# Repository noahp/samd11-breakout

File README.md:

[![GitHub Workflow
Status](https://img.shields.io/github/workflow/status/noahp/samd11-breakout/main-ci?style=for-the-badge)](https://github.com/noahp/samd11-breakout/actions)

# samd11 breakout

Little breakout for some spare samd11's.

Trying out https://debug-edge.io/ .

[Schematic PDF](hw/samd11-breakout.pdf)

## partlist

- usb c receptacle : https://octopart.com/search?q=usb4105
- DebugEdge connector : https://octopart.com/search?q=009159006061916
- arm debug cable : https://www.digikey.com/short/4cw7nq
- TVS diode : https://www.digikey.com/en/products/detail/stmicroelectronics/USBLC6-2SC6/1040559
- USB VSENSE diode : https://www.digikey.com/en/products/detail/on-semiconductor/BAT54XV2T1G/918321

Octopart bom with bonus arm connector and flux:

- https://octopart.com/bom-tool/GsivXDSs

## project directory structure

```bash
.
├── Dockerfile  # tests run inside this
├── hw  # hardware design files
│   ├── fp-lib-table
│   ├── GCT_USB4105-GF-A.kicad_mod  # USB connector footprint
│   ├── samd11-breakout_3d_afterdark.png  # render
│   ├── samd11-breakout_3d.png  # render
│   ├── samd11-breakout-cache.lib
│   ├── samd11-breakout-ibom.html  # saved copy of interactive BOM
│   ├── samd11-breakout.kibot.yaml  # kibot config file
│   ├── samd11-breakout.kicad_pcb
│   ├── samd11-breakout.pdf  # schematic PDF
│   ├── samd11-breakout.pro  # kicad project
│   ├── samd11-breakout.sch
│   ├── sym-lib-table
│   ├── thirdparty/  # some thirdpart libraries used for the hardware
│   ├── USB4105-GF-A.lib  # USB connector kicad lib
│   └── USB4105-GF-A.step  # USB connector 3d model
├── README.md
├── sw  # software
│   ├── samd11-breakout.atstart  # project file for https://start.atmel.com/
│   └── samd11-breakout.atzip   # unpacked example system downloaded from above
└── test.sh  # test script; builds docker image and runs tests in the container
```

## software

At the moment I'm just using the preset application with USB CDC, downloaded and
unpacked into the directory described above.

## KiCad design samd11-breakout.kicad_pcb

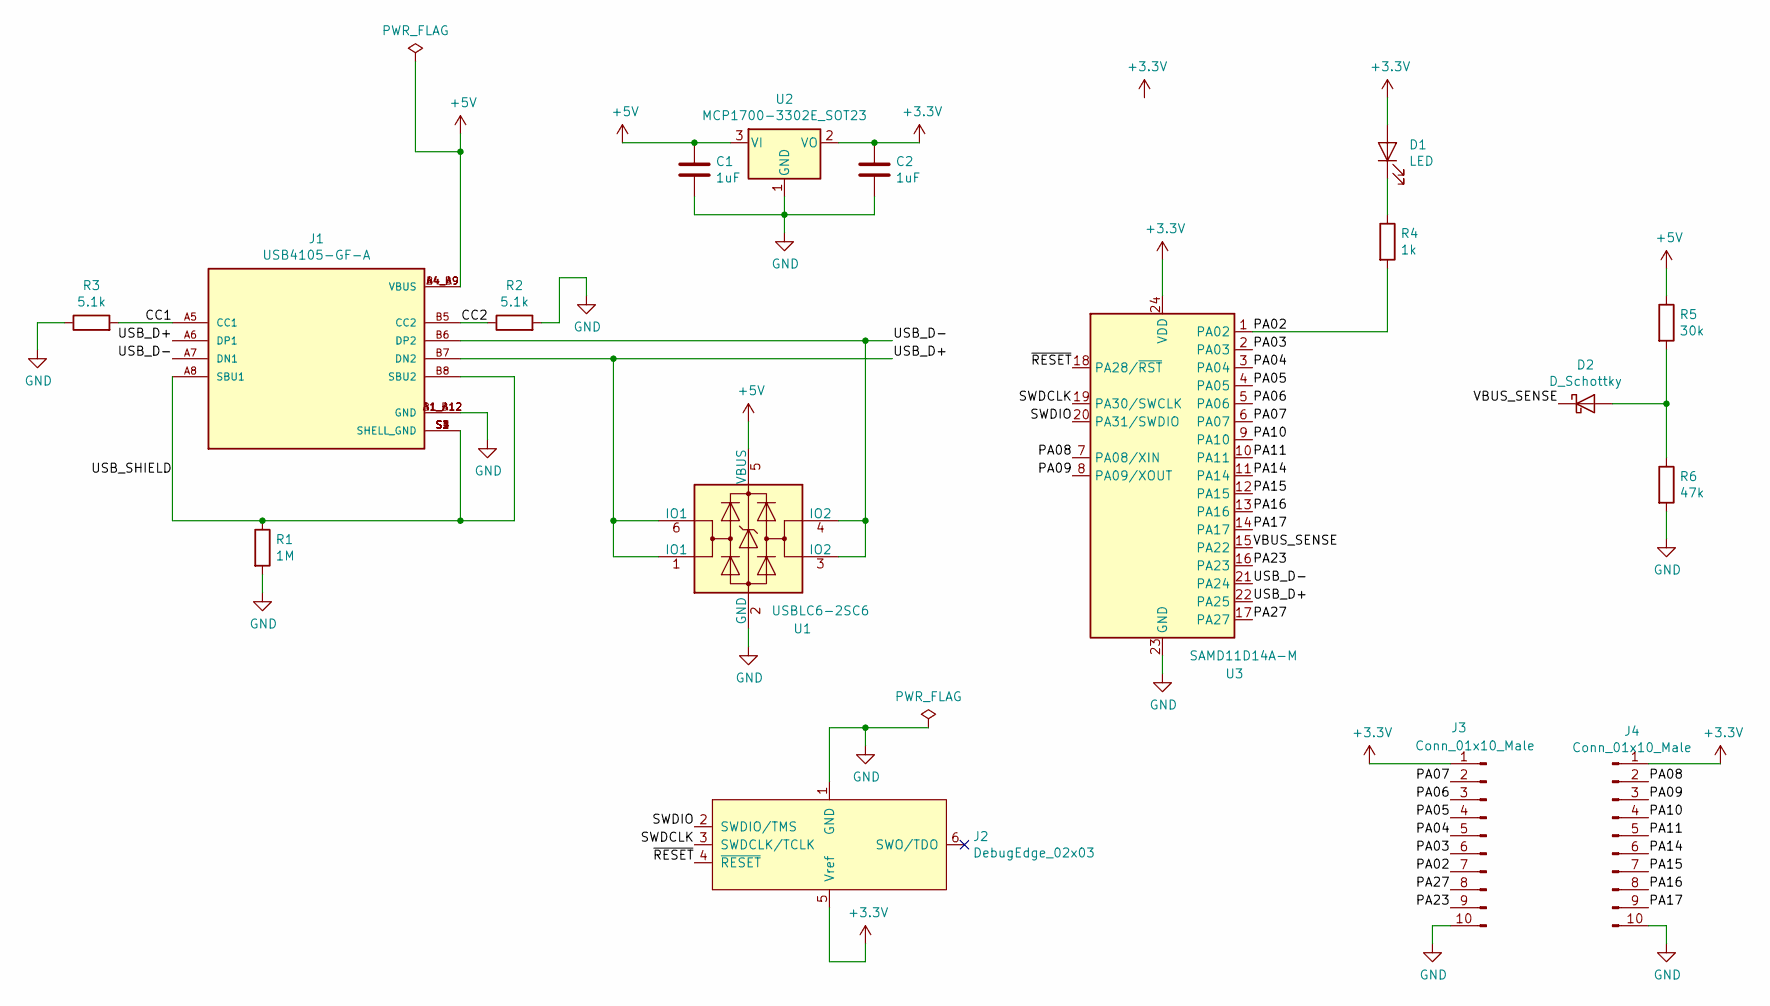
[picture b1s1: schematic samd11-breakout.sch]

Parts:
C1, C2: 1uF; C_0603_1608Metric
D1: LED; LED_0603_1608Metric
D2: D_Schottky; D_SOD-523
J1: USB4105-GF-A; GCT_USB4105-GF-A; PARTREV A3
J2: DebugEdge_02x03; DebugEdge_2x03_Target
J3, J4: Conn_01x10_Male; PinHeader_1x10_P2.54mm_Vertical
R1: 1M; R_0603_1608Metric
R2, R3: 5.1k; R_0603_1608Metric
R4: 1k; R_0603_1608Metric
R5: 30k; R_0603_1608Metric
R6: 47k; R_0603_1608Metric
U1: USBLC6-2SC6; SOT-23-6
U2: MCP1700-3302E_SOT23; SOT-23
U3: SAMD11D14A-M; QFN-24-1EP_4x4mm_P0.5mm_EP2.6x2.6mm

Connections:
+3V3: C2.1, D1.2 (A), J2.5 (Vref), J3.1, J4.1, U2.2 (VO), U3.24 (VDD)
+5V: C1.1, J1.A4_B9 (VBUS), J1.B4_A9 (VBUS), R5.1, U1.5 (VBUS), U2.3 (VI)
/CC1: J1.A5 (CC1), R3.2
/CC2: J1.B5 (CC2), R2.1
/PA02: J3.7, R4.2, U3.1 (PA02)
/PA03: J3.6, U3.2 (PA03)
/PA04: J3.5, U3.3 (PA04)
/PA05: J3.4, U3.4 (PA05)
/PA06: J3.3, U3.5 (PA06)
/PA07: J3.2, U3.6 (PA07)
/PA08: J4.2, U3.7 (PA08/XIN)
/PA09: J4.3, U3.8 (PA09/XOUT)
/PA10: J4.4, U3.9 (PA10)
/PA11: J4.5, U3.10 (PA11)
/PA14: J4.6, U3.11 (PA14)
/PA15: J4.7, U3.12 (PA15)
/PA16: J4.8, U3.13 (PA16)
/PA17: J4.9, U3.14 (PA17)
/PA23: J3.9, U3.16 (PA23)
/PA27: J3.8, U3.17 (PA27)
/SWDCLK: J2.3 (SWDCLK/TCLK), U3.19 (PA30/SWCLK)
/SWDIO: J2.2 (SWDIO/TMS), U3.20 (PA31/SWDIO)
/USB_D+: J1.A6 (DP1), J1.B7 (DN2), U1.1 (IO1), U1.6 (IO1), U3.22 (PA25)
/USB_D-: J1.A7 (DN1), J1.B6 (DP2), U1.3 (IO2), U1.4 (IO2), U3.21 (PA24)
/USB_SHIELD: J1.A8 (SBU1), J1.B8 (SBU2), J1.S1 (SHELL_GND), J1.S2 (SHELL_GND), J1.S3 (SHELL_GND), J1.S4 (SHELL_GND), R1.1
/VBUS_SENSE: D2.1 (K), U3.15 (PA22)
/~RESET: J2.4 (~RESET~), U3.18 (PA28/~RST)
GND: C1.2, C2.2, J1.A1_B12 (GND), J1.B1_A12 (GND), J2.1 (GND), J3.10, J4.10, R1.2, R2.2, R3.1, R6.2, U1.2 (GND), U2.1 (GND), U3.23 (GND)
unnamed: D1.1 (K), R4.1
unnamed: D2.2 (A), R5.2, R6.1

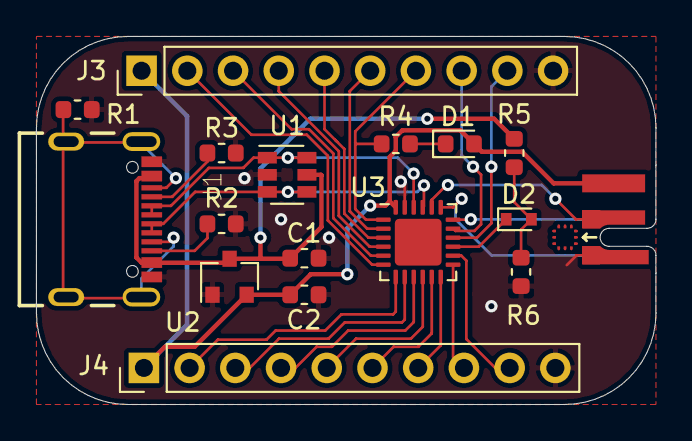
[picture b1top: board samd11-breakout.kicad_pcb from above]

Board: 2 copper layers, 34.4 x 20.4 mm, 17 parts (0 on the bottom side), 30 nets.

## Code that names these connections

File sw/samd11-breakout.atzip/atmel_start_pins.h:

/*
 * Code generated from Atmel Start.
 *
 * This file will be overwritten when reconfiguring your Atmel Start project.
 * Please copy examples or other code you want to keep to a separate file
 * to avoid losing it when reconfiguring.
 */
#ifndef ATMEL_START_PINS_H_INCLUDED
#define ATMEL_START_PINS_H_INCLUDED

#include <hal_gpio.h>

// SAMD11 has 8 pin functions

#define GPIO_PIN_FUNCTION_A 0
#define GPIO_PIN_FUNCTION_B 1
#define GPIO_PIN_FUNCTION_C 2
#define GPIO_PIN_FUNCTION_D 3
#define GPIO_PIN_FUNCTION_E 4
#define GPIO_PIN_FUNCTION_F 5
#define GPIO_PIN_FUNCTION_G 6
#define GPIO_PIN_FUNCTION_H 7

#define PA02 GPIO(GPIO_PORTA, 2)
#define PA22 GPIO(GPIO_PORTA, 22)
#define PA24 GPIO(GPIO_PORTA, 24)
#define PA25 GPIO(GPIO_PORTA, 25)

#endif // ATMEL_START_PINS_H_INCLUDED

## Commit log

2021-01-05 add DebugEdge submodule
2021-01-05 schematic done
2021-01-05 save board outline
2021-01-05 pin docker base image
2021-01-06 half routed
2021-01-08 ok that should do it
2021-01-08 3d render
2021-01-08 schematic pdf
2021-01-08 add partlist, fix usb connector lib
    Weirdly space sensitive:
    `# End Library` <- this is bad
    `#End Library` <- this is good
2021-01-08 add interactive bom output
2021-01-09 add silk text to back
2021-01-09 save bom
2021-01-09 after dark render
2021-01-14 move hw to subdir
2021-01-14 fix image path
2021-01-14 add goofy atmel START application
2021-01-14 add sw build to ci
2021-01-14 badges, fix ci branch
2021-01-24 fix silk overlap
2021-02-04 enable cdc? didn't work...
